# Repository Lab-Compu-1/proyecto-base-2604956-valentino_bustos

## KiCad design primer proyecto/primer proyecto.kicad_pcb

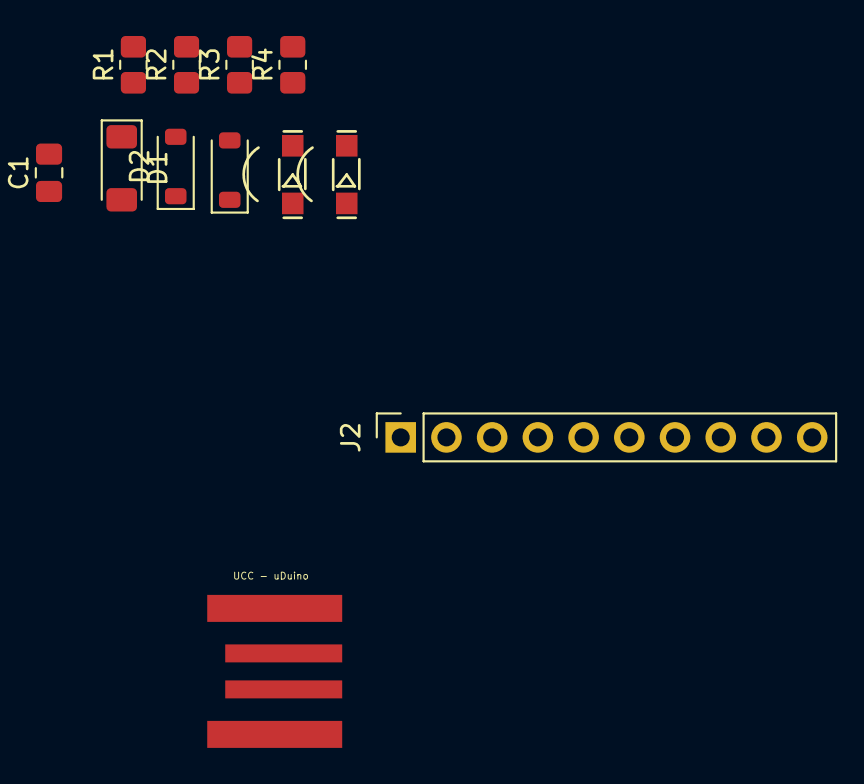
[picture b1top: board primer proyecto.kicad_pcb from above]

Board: 2 copper layers, 12 parts (0 on the bottom side), 9 nets, no tracks yet.

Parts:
C1: 0.1 u; C_0805_2012Metric_Pad1.18x1.45mm_HandSolder
D1: D; D_MiniMELF
D2, D3: 3.6V 1/2mW; D_SOD-123
D4: LED Green; LED.R
D5: LED; LED.R
J1: USB_A; USB_A_UCC
J2: Header; PinSocket_1x10_P2.54mm_Vertical
R1: 1.5KΩ 5% 1/8W; R_0805_2012Metric_Pad1.20x1.40mm_HandSolder
R2, R3: 68Ω 5% 1/8W; R_0805_2012Metric_Pad1.20x1.40mm_HandSolder
R4: 330Ω 5% 1/8W; R_0805_2012Metric_Pad1.20x1.40mm_HandSolder

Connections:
+5V: C1.1, D1.1 (K), D5.2 (A), J2.1, R1.1
GND: C1.2, D2.2 (A), D3.2 (A), J1.4 (GND), J2.2, R4.2
unnamed: D1.2 (A), J1.1 (VBUS)
unnamed: D2.1 (K), J1.2 (D-), R1.2, R2.1
unnamed: D3.1 (K), J1.3 (D+), R3.1
unnamed: D4.2 (A), J2.5
unnamed: D4.1 (K), R4.1
unnamed: J2.7, R2.2
unnamed: J2.8, R3.2

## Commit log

2026-05-22 Setting up GitHub Classroom Feedback
2026-05-29 mi primer commit y entreda de proyecto kicad
